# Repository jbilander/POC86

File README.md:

# POC86
PortZ Of Call 86 - An external co-processor slot for the A500 with a pass-through expansion edge.

FRONT SIDE &emsp;&emsp;&emsp;&emsp;&emsp;&emsp;&emsp;&emsp;&emsp;&emsp;&emsp;&emsp;&emsp; UNDER SIDE<br />

***
New Compact Edition board, no pass-through expansion edge:<br />
FRONT SIDE &emsp;&emsp;&emsp;&emsp;&emsp;&emsp;&emsp;&emsp;&emsp;&emsp;&emsp;&emsp;&emsp; UNDER SIDE<br />

***

86-pin connectors can be sourced from here:<br />
https://www.aliexpress.com/item/33029711948.html

***

***
When ordering make sure you select ENIG and goldfingers + send note about chamfering only on one side.
(Not relevant for the new compact edition board, No ENIG-goldfingers nor chamfering needed there, HASL is enough since the expansion edge is gone)
<br />
<br />

***

[![CC BY-SA 4.0][cc-by-sa-shield]][cc-by-sa]

This work is licensed under a
[Creative Commons Attribution-ShareAlike 4.0 International License][cc-by-sa].

[![CC BY-SA 4.0][cc-by-sa-image]][cc-by-sa]

[cc-by-sa]: http://creativecommons.org/licenses/by-sa/4.0/
[cc-by-sa-image]: https://licensebuttons.net/l/by-sa/4.0/88x31.png
[cc-by-sa-shield]: https://img.shields.io/badge/License-CC%20BY--SA%204.0-lightgrey.svg

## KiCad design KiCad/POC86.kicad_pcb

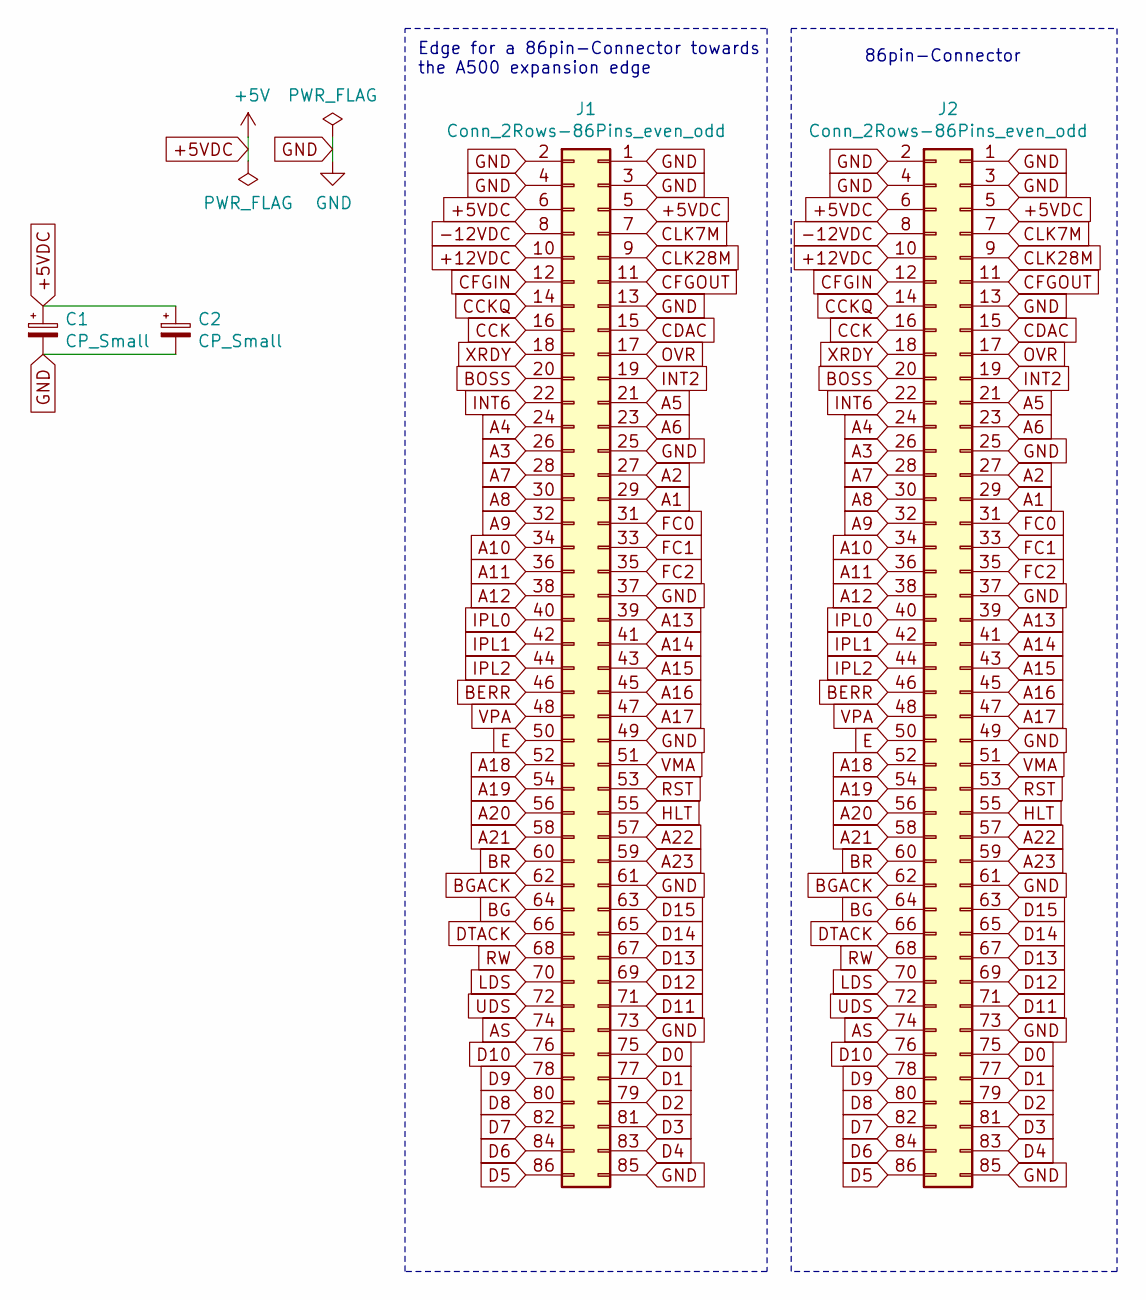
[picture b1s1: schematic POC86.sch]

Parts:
C1, C2: CP_Small; CP_Radial_D5.0mm_P2.50mm
J1: Conn_2Rows-86Pins_even_odd; A500_Mirrored_86pin_Edge
J2: Conn_2Rows-86Pins_even_odd; DIP-86_even_odd_W5.08mm

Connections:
+5VDC: C1.1, C2.1, J1.5, J1.6, J2.5, J2.6
+12VDC: J1.10, J2.10
-12VDC: J1.8, J2.8
A1: J1.29, J2.29
A2: J1.27, J2.27
A3: J1.26, J2.26
A4: J1.24, J2.24
A5: J1.21, J2.21
A6: J1.23, J2.23
A7: J1.28, J2.28
A8: J1.30, J2.30
A9: J1.32, J2.32
A10: J1.34, J2.34
A11: J1.36, J2.36
A12: J1.38, J2.38
A13: J1.39, J2.39
A14: J1.41, J2.41
A15: J1.43, J2.43
A16: J1.45, J2.45
A17: J1.47, J2.47
A18: J1.52, J2.52
A19: J1.54, J2.54
A20: J1.56, J2.56
A21: J1.58, J2.58
A22: J1.57, J2.57
A23: J1.59, J2.59
AS: J1.74, J2.74
BERR: J1.46, J2.46
BG: J1.64, J2.64
BGACK: J1.62, J2.62
BOSS: J1.20, J2.20
BR: J1.60, J2.60
CCK: J1.16, J2.16
CCKQ: J1.14, J2.14
CDAC: J1.15, J2.15
CFGIN: J1.12, J2.12
CFGOUT: J1.11, J2.11
CLK7M: J1.7, J2.7
CLK28M: J1.9, J2.9
D0: J1.75, J2.75
D1: J1.77, J2.77
D2: J1.79, J2.79
D3: J1.81, J2.81
D4: J1.83, J2.83
D5: J1.86, J2.86
D6: J1.84, J2.84
D7: J1.82, J2.82
D8: J1.80, J2.80
D9: J1.78, J2.78
D10: J1.76, J2.76
D11: J1.71, J2.71
D12: J1.69, J2.69
D13: J1.67, J2.67
D14: J1.65, J2.65
D15: J1.63, J2.63
DTACK: J1.66, J2.66
E: J1.50, J2.50
FC0: J1.31, J2.31
FC1: J1.33, J2.33
FC2: J1.35, J2.35
GND: C1.2, C2.2, J1.1, J1.2, J1.3, J1.4, J1.13, J1.25, J1.37, J1.49, J1.61, J1.73, J1.85, J2.1, J2.2, J2.3, J2.4, J2.13, J2.25, J2.37, J2.49, J2.61, J2.73, J2.85
HLT: J1.55, J2.55
INT2: J1.19, J2.19
INT6: J1.22, J2.22
IPL0: J1.40, J2.40
IPL1: J1.42, J2.42
IPL2: J1.44, J2.44
LDS: J1.70, J2.70
OVR: J1.17, J2.17
RST: J1.53, J2.53
RW: J1.68, J2.68
UDS: J1.72, J2.72
VMA: J1.51, J2.51
VPA: J1.48, J2.48
XRDY: J1.18, J2.18

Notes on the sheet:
Edge for a 86pin-Connector towards the A500 expansion edge
86pin-Connector

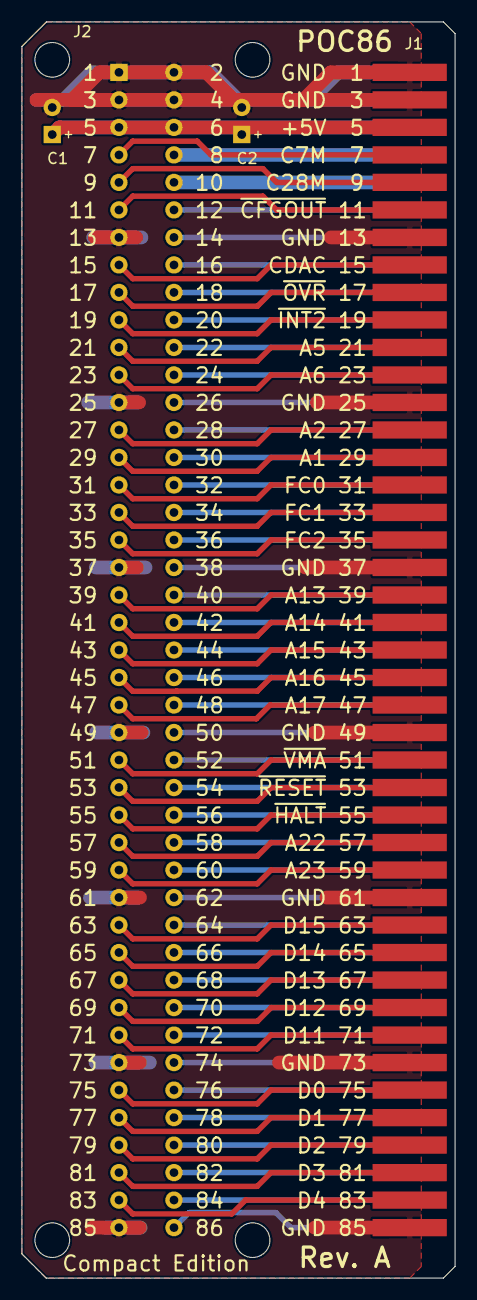
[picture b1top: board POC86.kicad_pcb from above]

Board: 2 copper layers, 40.0 x 116.0 mm, 4 parts (1 on the bottom side), 75 nets.

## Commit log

2022-04-05 added footprints
2022-04-05 added KiCAD-files
2022-04-05 added mounting holes and silkscreen pinout explanations
2022-04-06 added silkscreen on underside of board
2022-04-06 added C1,C2 radial THT-capacitors for +5V-rail
2022-04-06 added Revision to silkscreen print
2022-04-06 added images
2022-04-06 added schematic pdf
2022-04-06 Added LICENSE
2022-04-09 added J4-pin on CFGIN-line to easily patch through this signal to J3-edge if J2-slot is empty
2022-04-09 updated pics
2022-04-09 updated schematic pdf
2022-07-30 added pics
2022-08-22 Redesign to a more Compact Edition with no pass-through expansion edge
2022-08-22 added pics of compact edition board
2022-08-22 added revA schematic pdf for compact edition board

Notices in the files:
KiCad/POC86.kicad_pcb:
© 2022
